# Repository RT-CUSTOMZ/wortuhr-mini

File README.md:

# Einleitung

Kleinere Version der Original Campuswochen Wortuhr. 
Das Buchstabenlayout dieser WortUhr ist angelehnt an das Layout, welches von Frank Meyer verwendet wird.

Der Aufbau ist nun kompatibel mit 60 LED/m WS2812B/SK6812 LED Streifen. Um das zu erreichen ist die Rahmengröße reduziert auf 35cm Innenmaß. Hierzu eignet sich zum Beispiel der IKEA SANNAHED 35x35cm Rahmen. Die Steuerplatine ist auf das wesentliche beschränkt, die Stromversorgung übernehmen zwei generische DCDC Mini-560 Netzteile. Es wird weiterhin über einen Rundbuchsenanschluss mit 19-21V eingespeist. Um die Bestellung möglichst einfach zu gestalten werden die Power und Steuerplatine auf eine gemeinsame Platine gepaneled. (Siehe Kombiplatine THT)

Die Software und das Layout der Matrix von Frank Meyer wurden minimal angepasst.

Originaler Artikel: https://www.mikrocontroller.net/articles/WordClock_mit_WS2812

Originaler Aufbau: https://www.mikrocontroller.net/articles/Tutorial_-_Aufbau_WordClock_mit_WS2812

# Inhaltsverzeichnis
- [Wiki](https://github.com/RT-CUSTOMZ/wortuhr-mini/wiki)
- [Bauanleitung]([/wiki/Bauanleitung](https://github.com/RT-CUSTOMZ/wortuhr-mini/wiki/Bauanleitung))
- [Hardware](https://github.com/RT-CUSTOMZ/wortuhr-mini/wiki/Hardware-Material)
- [Software](https://github.com/RT-CUSTOMZ/wortuhr-mini/wiki/Software)

Copyright (c) 2014-2019 Frank Meyer - frank(at)fli4l.de

This program is free software; you can redistribute it and/or modify it under the terms of the GNU General Public License as published by the Free Software Foundation; either version 2 of the License, or (at your option) any later version.

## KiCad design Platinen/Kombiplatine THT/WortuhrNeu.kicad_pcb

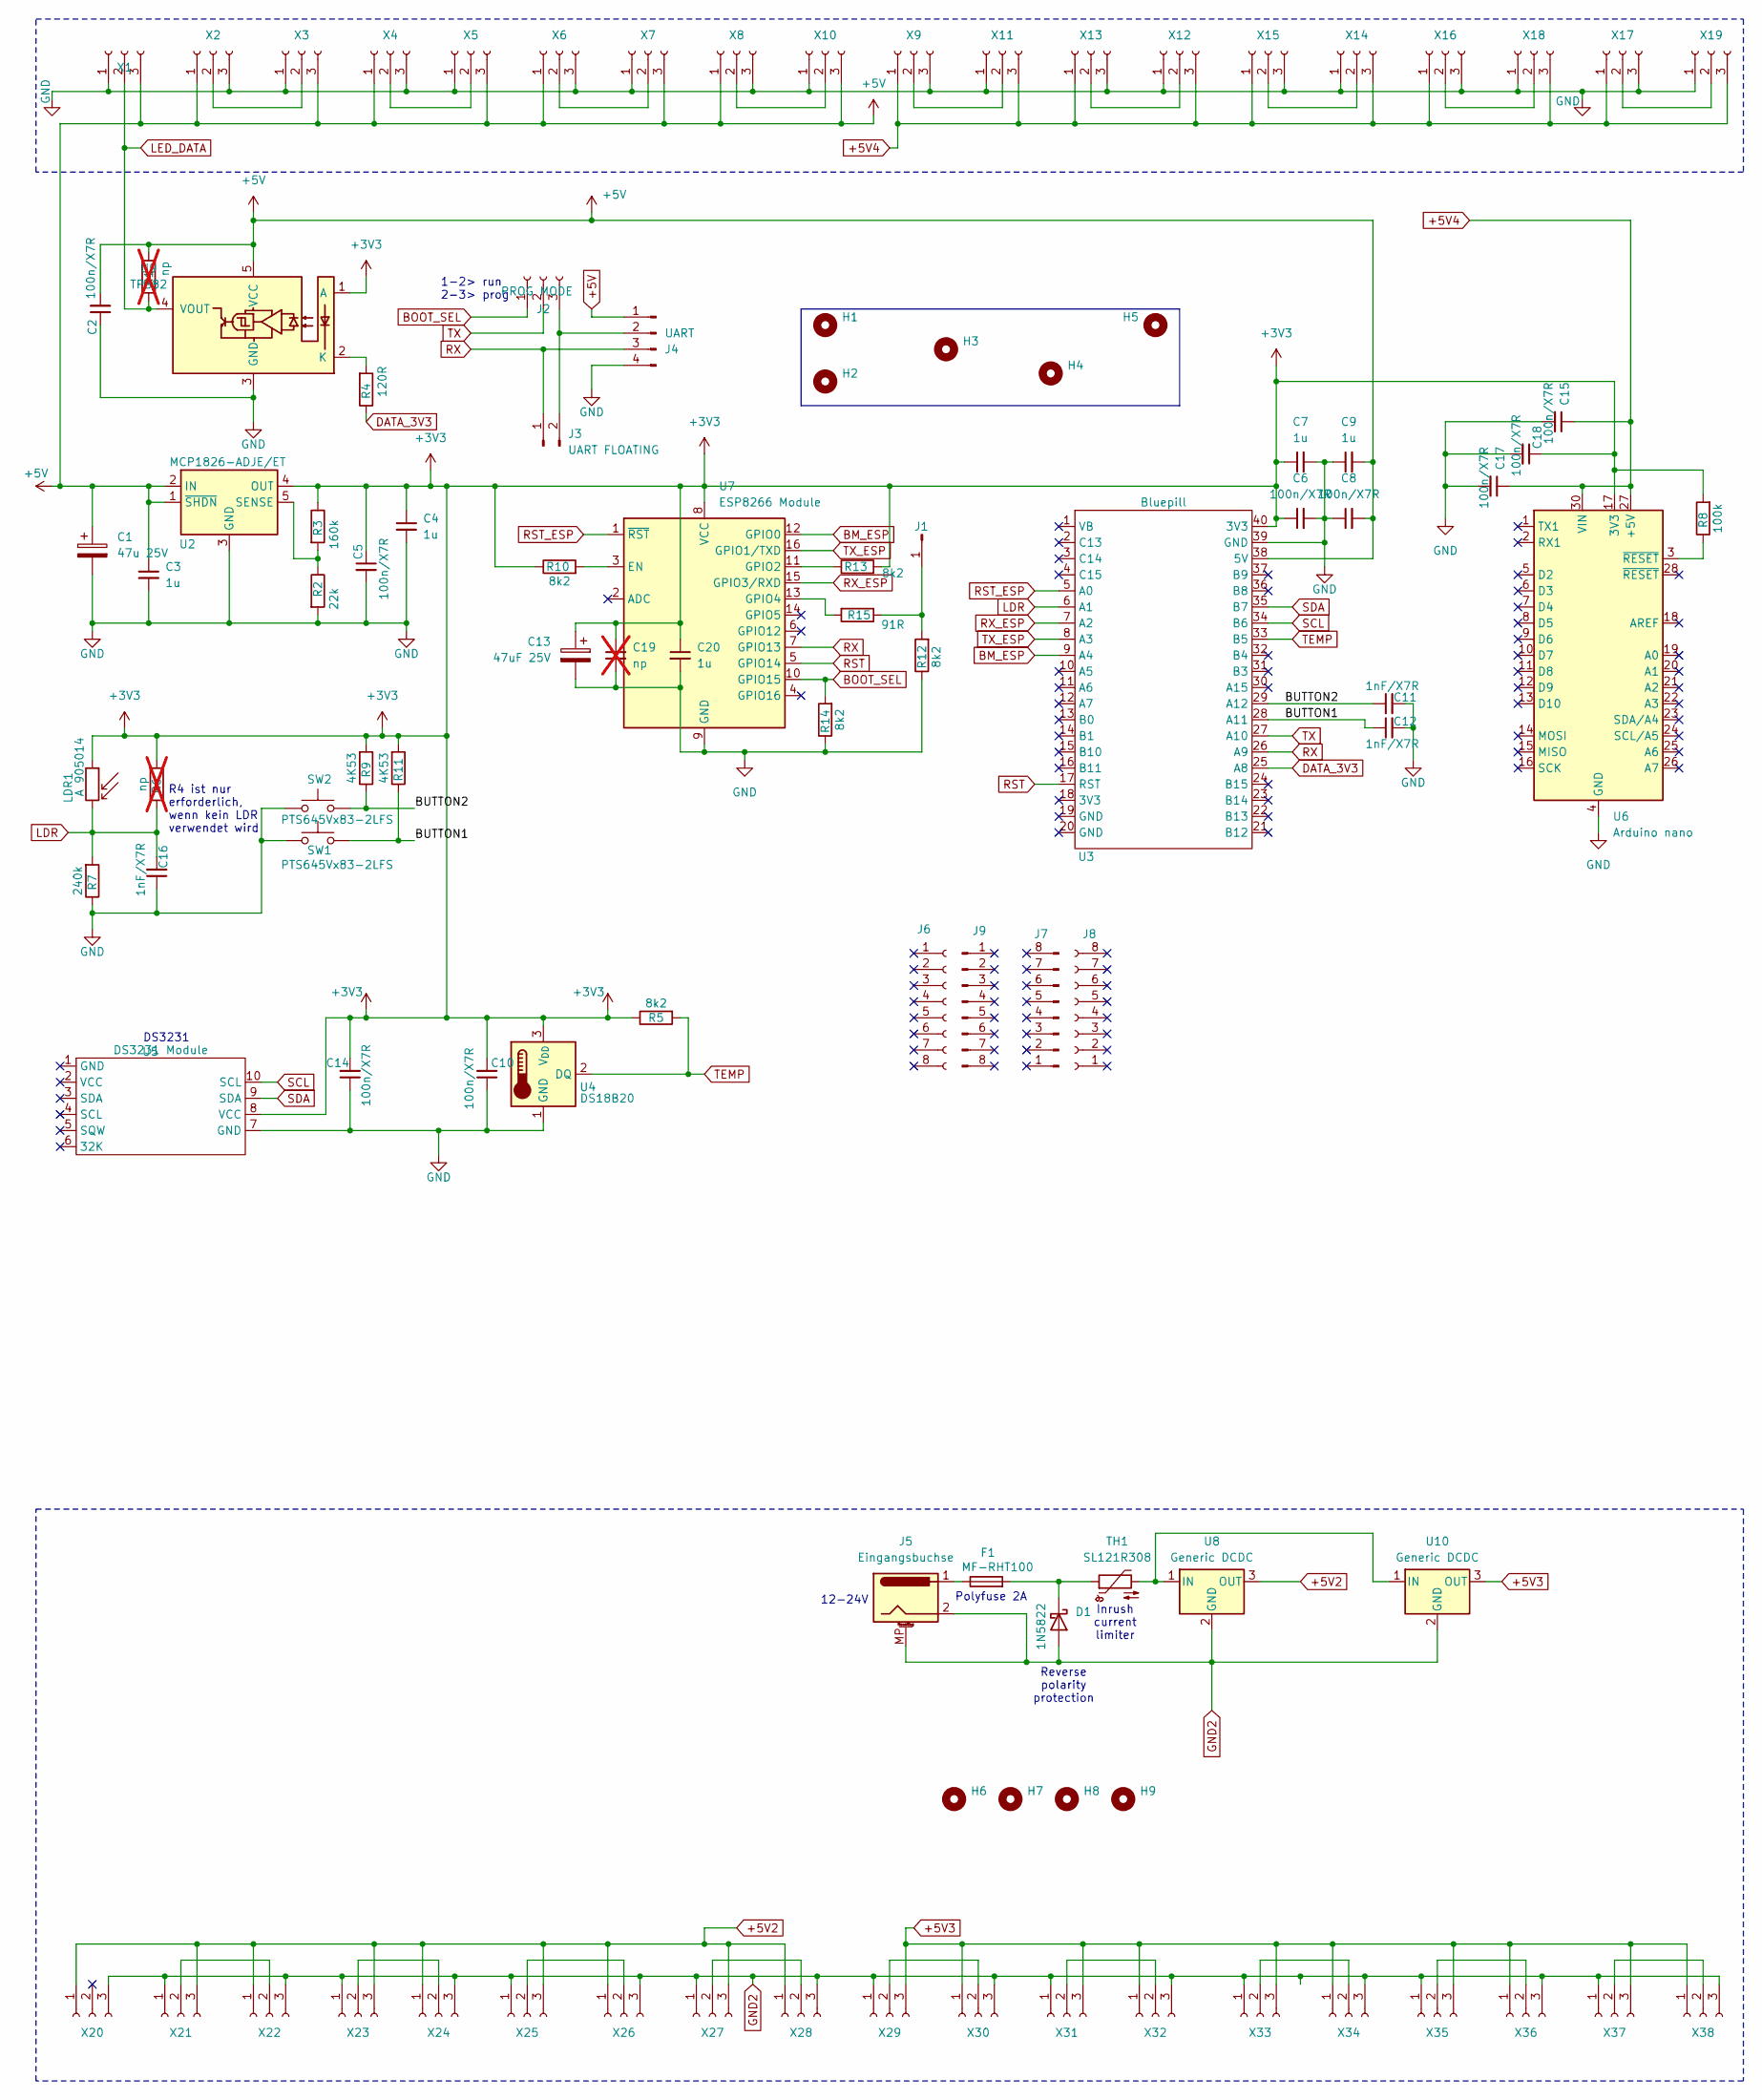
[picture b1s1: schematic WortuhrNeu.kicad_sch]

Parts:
C1: 47u 25V; CP_Radial_D10.0mm_P5.00mm
C2, C5, C6, C8, C10, C14, C15, C17, C18: 100n/X7R; C_Disc_D4.7mm_W2.5mm_P5.00mm
C3, C4, C7, C9, C20: 1u; C_Disc_D4.7mm_W2.5mm_P5.00mm
C11, C12, C16: 1nF/X7R; C_Disc_D4.7mm_W2.5mm_P5.00mm
C13: 47uF 25V; CP_Radial_D10.0mm_P5.00mm
C19: np; C_1812_4532Metric_Pad1.57x3.40mm_HandSolder; not fitted
D1: 1N5822; D_A-405_P2.54mm_Vertical_AnodeUp
F1: MF-RHT100; Fuse_Bourns_MF-RHT100
H1, H2, H3, H4, H5, H6, H7, H8, H9: MountingHole; MountingHole_3.2mm_M3_DIN965
J1: Conn_01x01_Pin; PinHeader_1x01_P2.54mm_Vertical
J2: PROG MODE; PinHeader_1x03_P2.54mm_Vertical
J3: UART FLOATING; PinHeader_1x02_P2.54mm_Vertical
J4: UART; PinHeader_1x04_P2.54mm_Vertical
J5: Eingangsbuchse; BarrelJack_GCT_DCJ200-10-A_Horizontal
J6, J7: Conn_01x08_Pin; PinHeader_1x08_P2.00mm_Vertical
J8, J9: Conn_01x08_Socket; PinSocket_1x08_P2.00mm_Vertical
LDR1: A 905014; R_LDR_4.9x4.2mm_P2.54mm_Vertical
R1, R6: np; R_Axial_DIN0207_L6.3mm_D2.5mm_P10.16mm_Horizontal; not fitted
R2: 22k; R_Axial_DIN0207_L6.3mm_D2.5mm_P10.16mm_Horizontal
R3: 160k; R_Axial_DIN0207_L6.3mm_D2.5mm_P10.16mm_Horizontal
R4: 120R; R_Axial_DIN0207_L6.3mm_D2.5mm_P10.16mm_Horizontal
R5, R10, R12, R13, R14: 8k2; R_Axial_DIN0207_L6.3mm_D2.5mm_P10.16mm_Horizontal
R7: 240k; R_Axial_DIN0207_L6.3mm_D2.5mm_P10.16mm_Horizontal
R8: 100k; R_Axial_DIN0207_L6.3mm_D2.5mm_P10.16mm_Horizontal
R9, R11: 4K53; R_Axial_DIN0207_L6.3mm_D2.5mm_P10.16mm_Horizontal
R15: 91R; R_Axial_DIN0207_L6.3mm_D2.5mm_P10.16mm_Horizontal
SW1, SW2: PTS645Vx83-2LFS; SW_Tactile_SPST_Angled_PTS645Vx83-2LFS
TH1: SL121R308; C_Disc_D12.0mm_W4.4mm_P7.75mm
U2: MCP1826-ADJE/ET; TO-263-5_TabPin3
U3: Bluepill
U4: DS18B20; TO-92_Inline
U5: DS3231 Module
U6: Arduino nano; Arduino_Nano
U7: ESP8266 Module; ESP-07
U8, U10: Generic DCDC; Converter_DCDC_RECOM_R-78B-2.0_THT
U9: TP582
X1, X2, X3, X4, X5, X6, X7, X8, X9, X10, X11, X12, X13, X14, X15, X16, X17, X18, X19, X20, X21, X22, X23, X24, X25, X26, X27, X28, X29, X30, X31, X32, X33, X34, X35, X36, X37, X38: Conn_01x03_Pin; PinSocket_1x03_P2.54mm_Vertical

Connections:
+3V3: C4.1, C5.1, C6.1, C7.1, C10.2, C13.1, C14.2, C18.1, C19.1, C20.1, LDR1.1, R3.1, R5.1, R6.2, R8.2, R9.2, R10.1, R11.2, R13.2, U2.4 (OUT), U3.40 (3V3), U4.3 (V_{DD}), U5.8 (VCC), U6.17 (3V3), U7.8 (VCC), U9.1 (A)
+5V: C1.1, C2.2, C3.1, C8.2, C9.2, J4.1, R1.2, U2.1 (~SHDN), U2.2 (IN), U3.38 (5V), U9.5 (VCC), X1.3, X2.1, X3.3, X4.1, X5.3, X6.1, X7.3, X8.1, X10.3
+5V2: U8.3 (OUT), X20.1, X21.3, X22.1, X23.3, X24.1, X25.3, X26.1, X27.3, X28.1
+5V3: U10.3 (OUT), X29.3, X30.1, X31.3, X32.1, X33.3, X34.1, X35.3, X36.1, X37.3, X38.1
+5V4: C15.1, C17.1, U6.27 (+5V), U6.30 (VIN), X9.1, X11.3, X12.3, X13.1, X14.3, X15.1, X16.1, X17.1, X18.3, X19.3
/BUTTON1: C12.1, R11.1, SW1.1, U3.28 (A11)
/BUTTON2: C11.1, R9.1, SW2.1, U3.29 (A12)
BM_ESP: U3.9 (A4), U7.12 (GPIO0)
BOOT_SEL: J2.1, R14.2, U7.10 (GPIO15)
DATA_3V3: R4.1, U3.25 (A8)
GND: C1.2, C2.1, C3.2, C4.2, C5.2, C6.2, C7.2, C8.1, C9.1, C10.1, C11.2, C12.2, C13.2, C14.1, C15.2, C16.1, C17.2, C18.2, C19.2, C20.2, J4.4, R2.2, R7.1, R12.1, R14.1, SW1.2, SW2.2, U2.3 (GND), U3.39 (GND), U4.1 (GND), U5.7 (GND), U6.4 (GND), U6.29 (GND), U7.9 (GND), U9.3 (GND), X1.1, X2.3, X3.1, X4.3, X5.1, X6.3, X7.1, X8.3, X9.3, X10.1, X11.1, X12.1, X13.3, X14.1, X15.3, X16.3, X17.3, X18.1, X19.1
GND2: D1.2 (A), J5.2, J5.MP (MountPin_MP), U8.2 (GND), U10.2 (GND), X20.3, X21.1, X22.3, X23.1, X24.3, X25.1, X26.3, X27.1, X28.3, X29.1, X30.3, X31.1, X32.3, X33.1, X34.3, X35.1, X36.3, X37.1, X38.3
LDR: C16.2, LDR1.2, R6.1, R7.2, U3.6 (A1)
LED_DATA: R1.1, U9.4 (VOUT), X1.2
unnamed: D1.1 (K), F1.2, TH1.1
unnamed: F1.1, J5.1
unnamed: J1.1 (Pin_1_1), R12.2, R15.1
unnamed: J2.3, J3.2, J4.2
unnamed: R8.1, U6.3 (~RESET)
unnamed: R2.1, R3.2, U2.5 (SENSE)
unnamed: R10.2, U7.3 (EN)
unnamed: R13.1, U7.11 (GPIO2)
unnamed: R15.2, U7.13 (GPIO4)
unnamed: R4.2, U9.2 (K)
unnamed: TH1.2, U8.1 (IN), U10.1 (IN)
unnamed: X2.2, X3.2
unnamed: X4.2, X5.2
unnamed: X6.2, X7.2
unnamed: X8.2, X10.2
unnamed: X9.2, X11.2
unnamed: X12.2, X13.2
unnamed: X14.2, X15.2
unnamed: X16.2, X18.2
unnamed: X17.2, X19.2
unnamed: X21.2, X22.2
unnamed: X23.2, X24.2
unnamed: X25.2, X26.2
unnamed: X27.2, X28.2
unnamed: X29.2, X30.2
unnamed: X31.2, X32.2
unnamed: X33.2, X34.2
unnamed: X35.2, X36.2
unnamed: X37.2, X38.2
RST: U3.17 (RST), U7.5 (GPIO14)
RST_ESP: U3.5 (A0), U7.1 (~RST)
RX: J3.1, J4.3, U3.26 (A9), U7.7 (GPIO13)
RX_ESP: U3.7 (A2), U7.15 (GPIO3/RXD)
SCL: U3.34 (B6), U5.10 (SCL)
SDA: U3.35 (B7), U5.9 (SDA)
TEMP: R5.2, U3.33 (B5), U4.2 (DQ)
TX: J2.2, U3.27 (A10)
TX_ESP: U3.8 (A3), U7.16 (GPIO1/TXD)

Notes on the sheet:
R4 ist nur erforderlich, wenn kein LDR verwendet wird
12-24V
DS3231
Polyfuse 2A
Reverse polarity protection
Inrush current limiter
1-2> run 2-3> prog

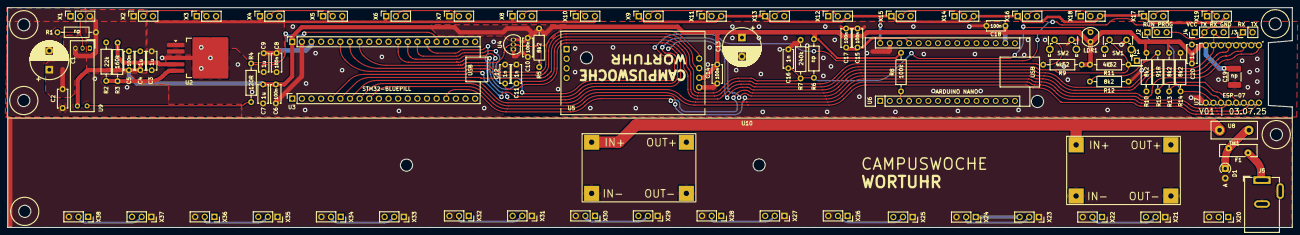
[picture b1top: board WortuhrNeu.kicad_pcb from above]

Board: 2 copper layers, 339.0 x 58.0 mm, 102 parts (0 on the bottom side), 52 nets.

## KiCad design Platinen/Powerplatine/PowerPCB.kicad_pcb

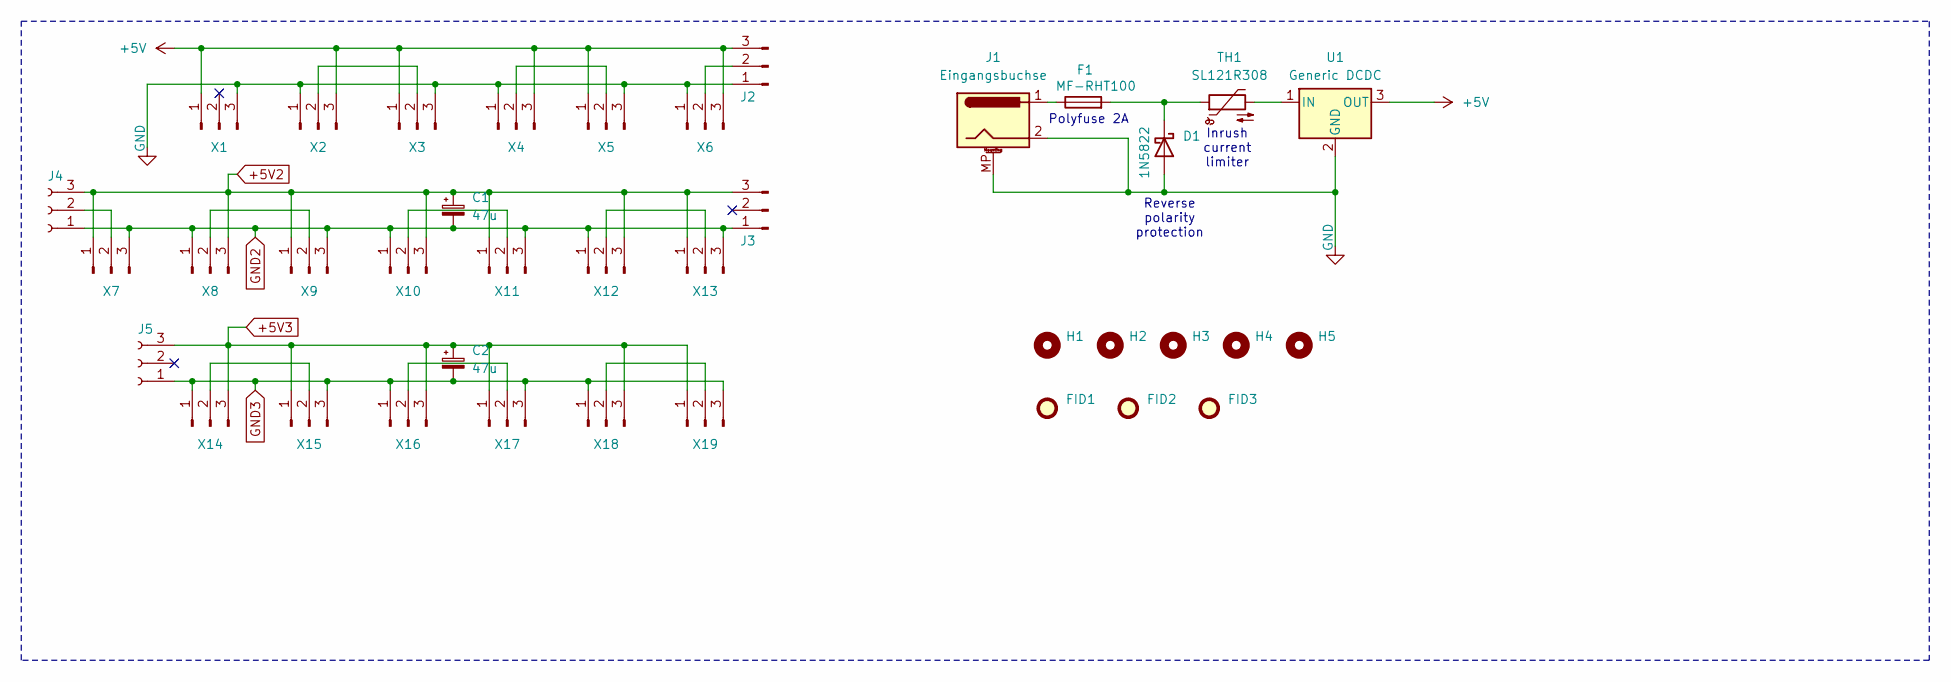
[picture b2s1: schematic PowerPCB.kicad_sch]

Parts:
C1, C2: 47u; CP_Radial_D8.0mm_P5.00mm
D1: 1N5822; D_A-405_P2.54mm_Vertical_AnodeUp
F1: MF-RHT100; Fuse_Bourns_MF-RHT100
FID1, FID2, FID3: Fiducial; Fiducial_1.5mm_Mask3mm
H1, H2, H3, H4, H5: MountingHole; MountingHole_3.2mm_M3_DIN965
J1: Eingangsbuchse; BarrelJack_GCT_DCJ200-10-A_Horizontal
J2, J3: Conn_01x03_Pin; PinHeader_2x02_P2.54mm_Horizontal
J4, J5: Conn_01x03_Socket; PinSocket_2x02_P2.54mm_Horizontal
TH1: SL121R308; C_Disc_D12.0mm_W4.4mm_P7.75mm
U1: Generic DCDC; Converter_DCDC_RECOM_R-78B-2.0_THT
X1, X2, X3, X4, X5, X6, X7, X8, X9, X10, X11, X12, X13, X14, X15, X16, X17, X18, X19: Conn_01x03_Pin; PinHeader_1x03_P2.54mm_Vertical

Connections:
+5V: J2.3, U1.3 (OUT), X1.1, X2.3, X3.1, X4.3, X5.1, X6.3
+5V2: C1.1, J3.3, J4.3, X7.1, X8.3, X9.1, X10.3, X11.1, X12.3, X13.1
+5V3: C2.1, J5.3, X14.3, X15.1, X16.3, X17.1, X18.3, X19.1
GND: D1.2 (A), J1.2, J1.MP (MountPin), J2.1, U1.2 (GND), X1.3, X2.1, X3.3, X4.1, X5.3, X6.1
GND2: C1.2, J3.1, J4.1, X7.3, X8.1, X9.3, X10.1, X11.3, X12.1, X13.3
GND3: C2.2, J5.1, X14.1, X15.3, X16.1, X17.3, X18.1, X19.3
unnamed: D1.1 (K), F1.2, TH1.1
unnamed: F1.1, J1.1
unnamed: J2.2, X6.2
unnamed: J4.2, X7.2
unnamed: TH1.2, U1.1 (IN)
unnamed: X2.2, X3.2
unnamed: X4.2, X5.2
unnamed: X8.2, X9.2
unnamed: X10.2, X11.2
unnamed: X12.2, X13.2
unnamed: X14.2, X15.2
unnamed: X16.2, X17.2
unnamed: X18.2, X19.2

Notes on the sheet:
Polyfuse 2A
Inrush current limiter
Reverse polarity protection

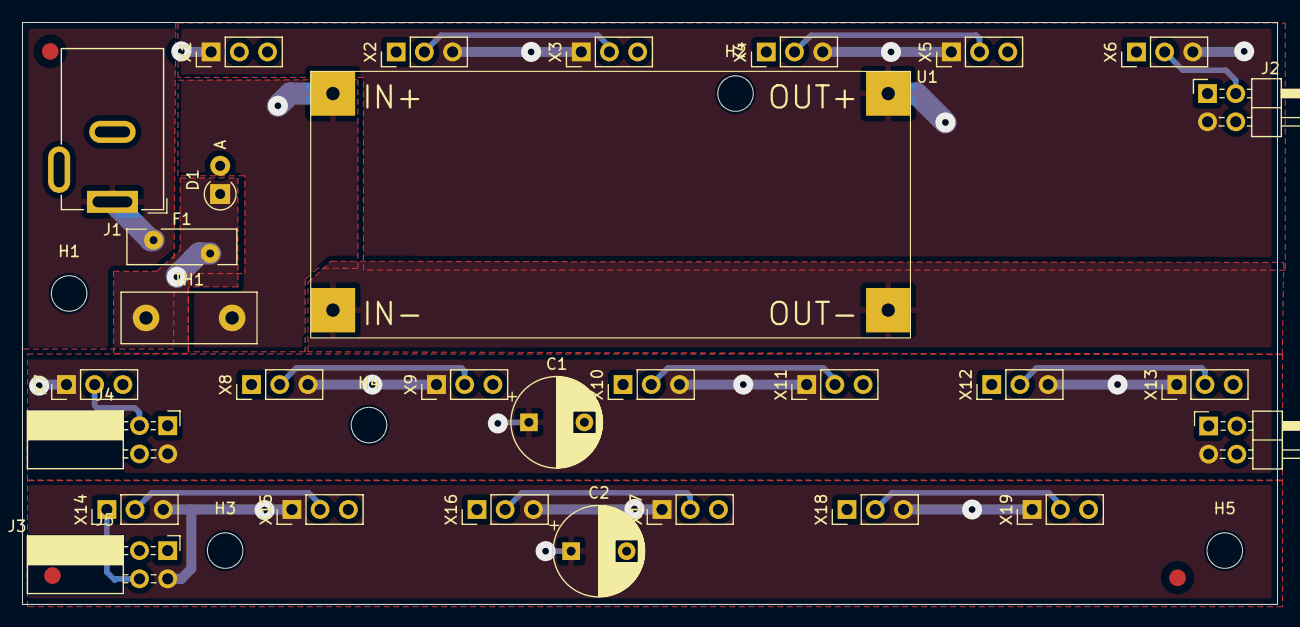
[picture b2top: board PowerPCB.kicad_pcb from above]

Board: 2 copper layers, 113.0 x 52.4 mm, 38 parts (0 on the bottom side), 19 nets.

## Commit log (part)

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2025-07-10 Changed file structure
2025-07-14 Added power PCB/protection circuits
2025-07-14 Changed pins to sockets, added image
2025-07-14 added letter matrix pdf v1
2025-07-19 Adjusted letter matrix and added stencil verśion
2025-07-19 added file for base plate layout/laser
2025-07-20 added horizonzal and vertical lasercut pieces
2025-07-22 added trotec template
2025-07-24 added baseplate
2025-07-24 ADJUSTED CUTS FOR BASE PLATE
2026-05-03 Combied pcbs, added smd version
2026-05-03 Combied pcbs, added smd version (#3)
2026-05-04 Implement some of the changes requested in issue 1
2026-05-28 Changes to Kombiplatine THT
2026-05-28 Merged major changes for this years wordclock (#5)
    * Combied pcbs, added smd version
    * Implement some of the changes requested in issue 1
    * Changes to Kombiplatine THT
    ---------
2026-05-28 Switched gpio4&5 on the esp for both boards
2026-05-28 Moved J1 closer to STM32 for OTA cable(SMD)
